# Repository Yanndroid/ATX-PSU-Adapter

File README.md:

# ATX PSU Adapter

This simple breakout board for a 24-pin ATX power supply provides 12V, 5V, 3.3V, and standby 5V. Additionally, it also has a small circuit to control the PSU.

Personally, I'm using this PCB to power my Raspberry Pi via the standby 5V line and can automatically turn the PSU on or off for other devices that also draw power from the PSU.

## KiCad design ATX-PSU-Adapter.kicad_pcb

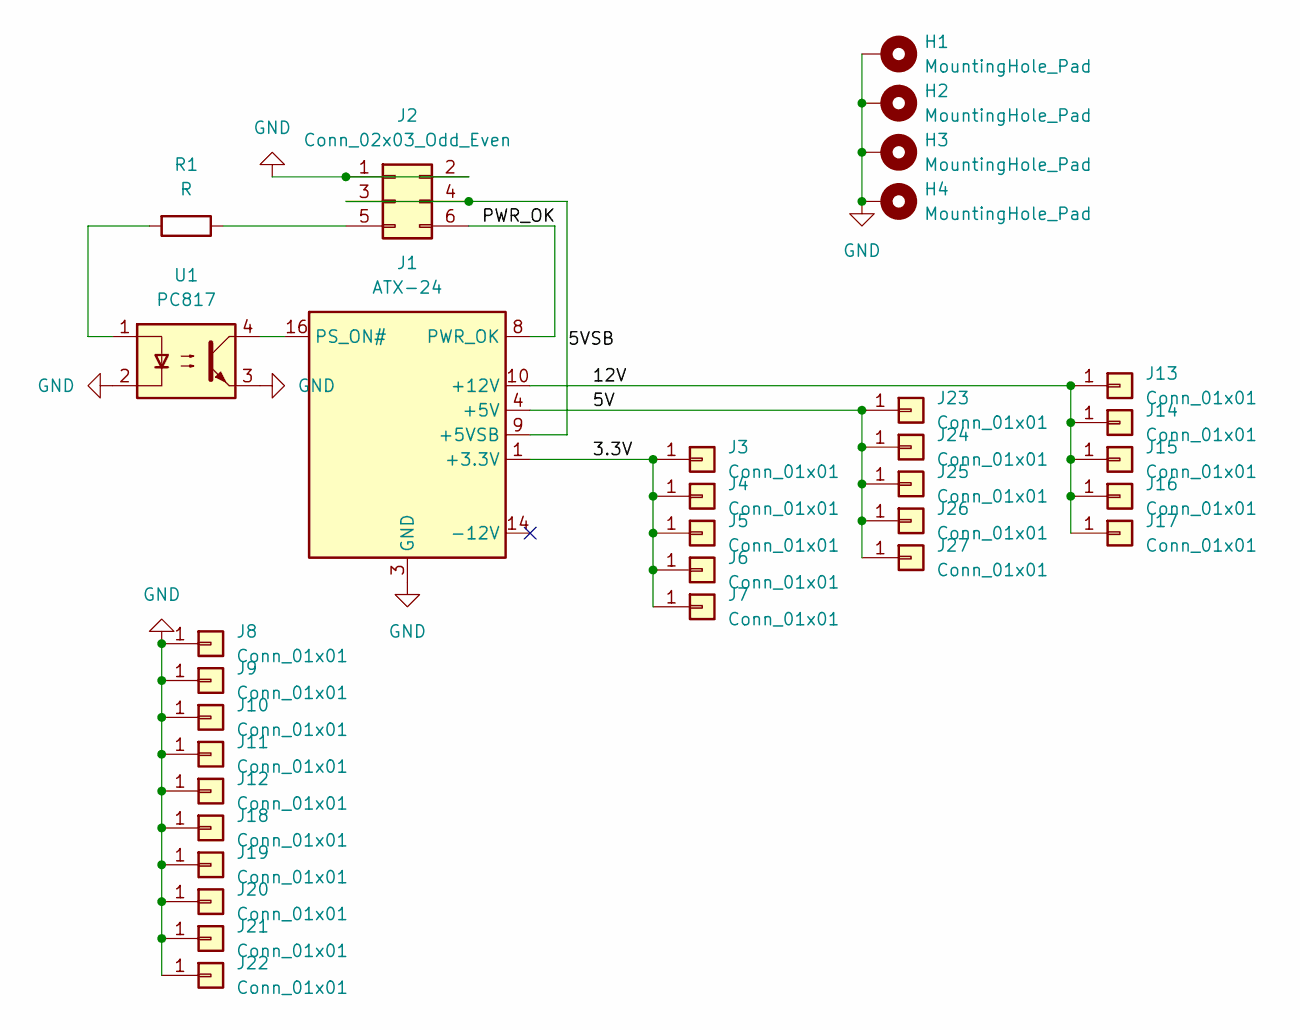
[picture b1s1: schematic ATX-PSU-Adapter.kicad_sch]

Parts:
H1, H2, H3, H4: MountingHole_Pad; MountingHole_2.5mm_Pad
J1: ATX-24; Molex_Mini-Fit_Jr_5566-24A_2x12_P4.20mm_Vertical
J2: Conn_02x03_Odd_Even; PinHeader_2x03_P2.54mm_Vertical
J3, J8, J13, J18, J23: Conn_01x01; SolderWire-0.5sqmm_1x01_D0.9mm_OD2.3mm
J4, J5, J6, J9, J10, J11, J14, J15, J16, J19, J20, J21, J24, J25, J26: Conn_01x01; SolderWire-0.75sqmm_1x01_D1.25mm_OD2.3mm
J7, J12, J17, J22, J27: Conn_01x01; SolderWire-1sqmm_1x01_D1.4mm_OD2.7mm
R1: R; R_Axial_DIN0207_L6.3mm_D2.5mm_P10.16mm_Horizontal
U1: PC817; DIP-4_W7.62mm

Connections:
/3.3V: J1.1 (+3.3V), J1.2 (+3.3V), J1.12 (+3.3V), J1.13 (+3.3V), J3.1, J4.1, J5.1, J6.1, J7.1
/5V: J1.4 (+5V), J1.6 (+5V), J1.21 (+5V), J1.22 (+5V), J1.23 (+5V), J23.1, J24.1, J25.1, J26.1, J27.1
/5VSB: J1.9 (+5VSB), J2.3, J2.4
/12V: J1.10 (+12V), J1.11 (+12V), J13.1, J14.1, J15.1, J16.1, J17.1
/PWR_OK: J1.8 (PWR_OK), J2.6
GND: H1.1, H2.1, H3.1, H4.1, J1.3 (GND), J1.5 (GND), J1.7 (GND), J1.15 (GND), J1.17 (GND), J1.18 (GND), J1.19 (GND), J1.24 (GND), J2.1, J2.2, J8.1, J9.1, J10.1, J11.1, J12.1, J18.1, J19.1, J20.1, J21.1, J22.1, U1.2, U1.3
unnamed: J1.16 (PS_ON#), U1.4
unnamed: J2.5, R1.1
unnamed: R1.2, U1.1

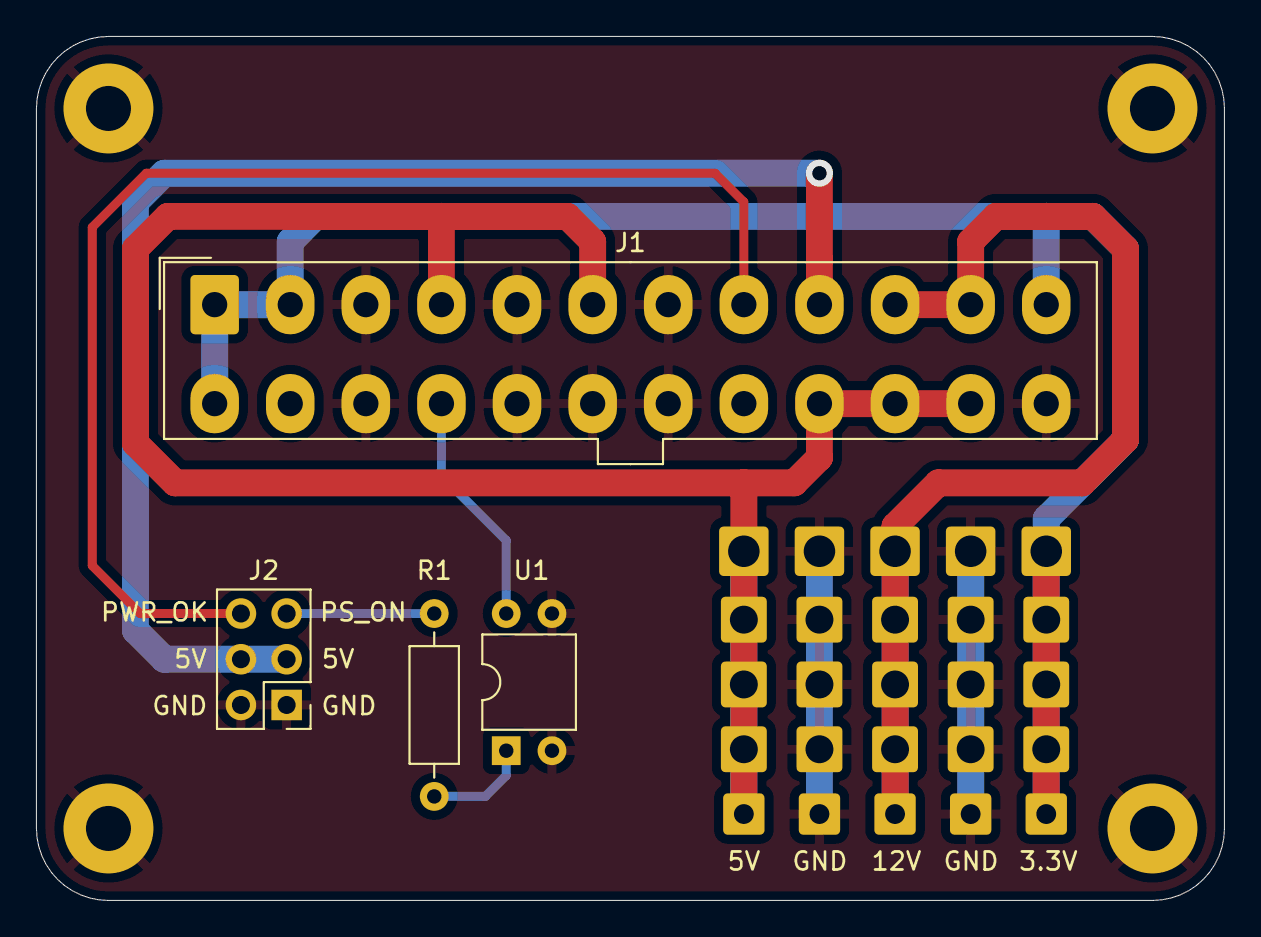
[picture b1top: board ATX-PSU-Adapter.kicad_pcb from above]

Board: 2 copper layers, 66.0 x 48.0 mm, 33 parts (0 on the bottom side), 9 nets.

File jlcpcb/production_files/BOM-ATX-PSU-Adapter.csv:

Comment,Designator,Footprint,LCSC
Conn_01x01,J5,SolderWire-0.75sqmm_1x01_D1.25mm_OD2.3mm,
ATX-24,J1,Molex_Mod_Mini-Fit_Jr_5566-24A_2x12_P4.20mm_Vertical,
PC817,U1,DIP-4_W7.62mm,
MountingHole_Pad,H1,MountingHole_2.5mm_Pad,
MountingHole_Pad,H2,MountingHole_2.5mm_Pad,
Conn_01x01,J7,SolderWire-1sqmm_1x01_D1.4mm_OD2.7mm,
Conn_01x01,J3,SolderWire-0.5sqmm_1x01_D0.9mm_OD2.3mm,
Conn_01x01,J6,SolderWire-0.75sqmm_1x01_D1.25mm_OD2.3mm,
Conn_01x01,J4,SolderWire-0.75sqmm_1x01_D1.25mm_OD2.3mm,
MountingHole_Pad,H4,MountingHole_2.5mm_Pad,
R,R1,R_Axial_DIN0207_L6.3mm_D2.5mm_P10.16mm_Horizontal,
MountingHole_Pad,H3,MountingHole_2.5mm_Pad,
Conn_02x03_Odd_Even,J2,PinHeader_2x03_P2.54mm_Vertical,
Conn_01x01,J23,SolderWire-0.5sqmm_1x01_D0.9mm_OD2.3mm,
Conn_01x01,J22,SolderWire-1sqmm_1x01_D1.4mm_OD2.7mm,
Conn_01x01,J16,SolderWire-0.75sqmm_1x01_D1.25mm_OD2.3mm,
Conn_01x01,J12,SolderWire-1sqmm_1x01_D1.4mm_OD2.7mm,
Conn_01x01,J25,SolderWire-0.75sqmm_1x01_D1.25mm_OD2.3mm,
Conn_01x01,J20,SolderWire-0.75sqmm_1x01_D1.25mm_OD2.3mm,
Conn_01x01,J10,SolderWire-0.75sqmm_1x01_D1.25mm_OD2.3mm,
Conn_01x01,J14,SolderWire-0.75sqmm_1x01_D1.25mm_OD2.3mm,
Conn_01x01,J19,SolderWire-0.75sqmm_1x01_D1.25mm_OD2.3mm,
Conn_01x01,J13,SolderWire-0.5sqmm_1x01_D0.9mm_OD2.3mm,
Conn_01x01,J27,SolderWire-1sqmm_1x01_D1.4mm_OD2.7mm,
Conn_01x01,J17,SolderWire-1sqmm_1x01_D1.4mm_OD2.7mm,
Conn_01x01,J9,SolderWire-0.75sqmm_1x01_D1.25mm_OD2.3mm,
Conn_01x01,J11,SolderWire-0.75sqmm_1x01_D1.25mm_OD2.3mm,
Conn_01x01,J8,SolderWire-0.5sqmm_1x01_D0.9mm_OD2.3mm,
Conn_01x01,J21,SolderWire-0.75sqmm_1x01_D1.25mm_OD2.3mm,
Conn_01x01,J15,SolderWire-0.75sqmm_1x01_D1.25mm_OD2.3mm,
Conn_01x01,J24,SolderWire-0.75sqmm_1x01_D1.25mm_OD2.3mm,
Conn_01x01,J18,SolderWire-0.5sqmm_1x01_D0.9mm_OD2.3mm,
Conn_01x01,J26,SolderWire-0.75sqmm_1x01_D1.25mm_OD2.3mm,

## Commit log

2023-09-23 Replace ATX Connector
2023-09-23 Replace pinheader
2023-09-23 Adjust text
2023-09-23 Switch 5VSB and GND
2023-09-23 Production files
2023-10-17 Fix: ATX Connector Footprint, Optocoupler wiring
2023-10-17 README
2024-04-02 Replace ATX connector, wiring and layout
